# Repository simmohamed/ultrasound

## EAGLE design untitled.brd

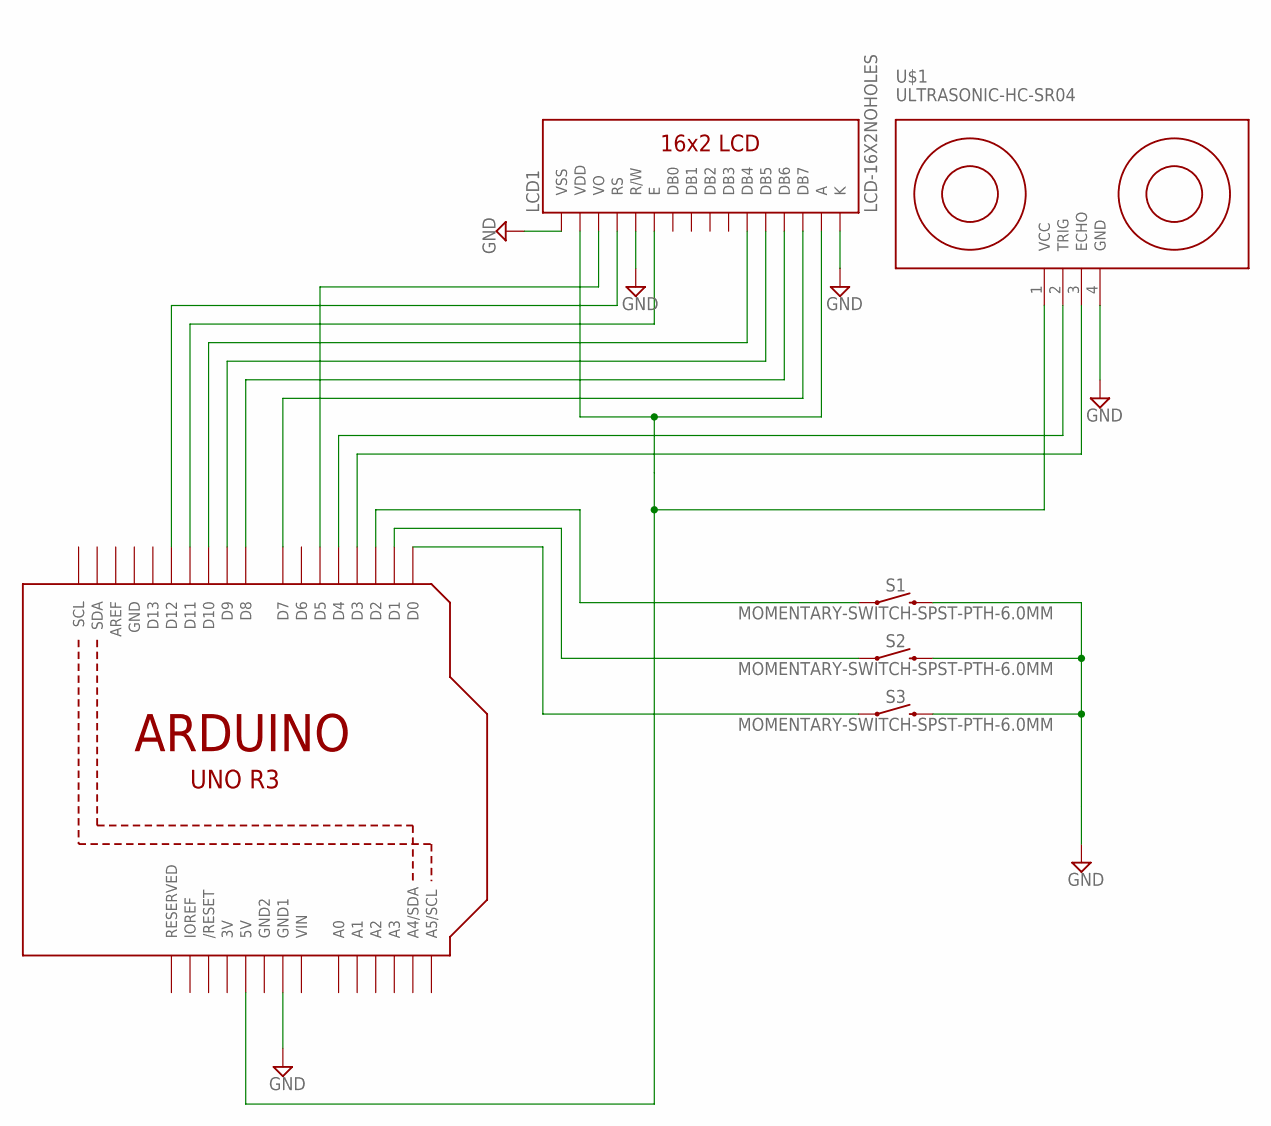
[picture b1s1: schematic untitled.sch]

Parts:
LCD1: LCD-16X2NOHOLES; LCD-16X2_NOHOLESNOSILK
S1, S2, S3: MOMENTARY-SWITCH-SPST-PTH-6.0MM; TACTILE_SWITCH_PTH_6.0MM
U1: ARDUINOR3-BPLACE
U$1: ULTRASONIC-HC-SR04

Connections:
3V: U1.3V
GND: LCD1.1 (VSS), LCD1.5 (R/W), LCD1.16 (K), S1.3 (2), S2.3 (2), S3.3 (2), U1.GND, U1.GND1, U$1.4 (GND)
GND2: U1.GND2
unnamed: LCD1.6 (E), U1.D11
unnamed: LCD1.4 (RS), U1.D12
unnamed: LCD1.11 (DB4), U1.D10
unnamed: LCD1.12 (DB5), U1.D9
unnamed: LCD1.13 (DB6), U1.D8
unnamed: LCD1.14 (DB7), U1.D7
unnamed: LCD1.2 (VDD), LCD1.15 (A), U1.5V, U$1.1 (VCC)
unnamed: LCD1.3 (VO), U1.D5
unnamed: U1.D3, U$1.3 (ECHO)
unnamed: U1.D4, U$1.2 (TRIG)
unnamed: S3.1, U1.D0
unnamed: S2.1, U1.D1
unnamed: S1.1, U1.D2
VIN: U1.VIN

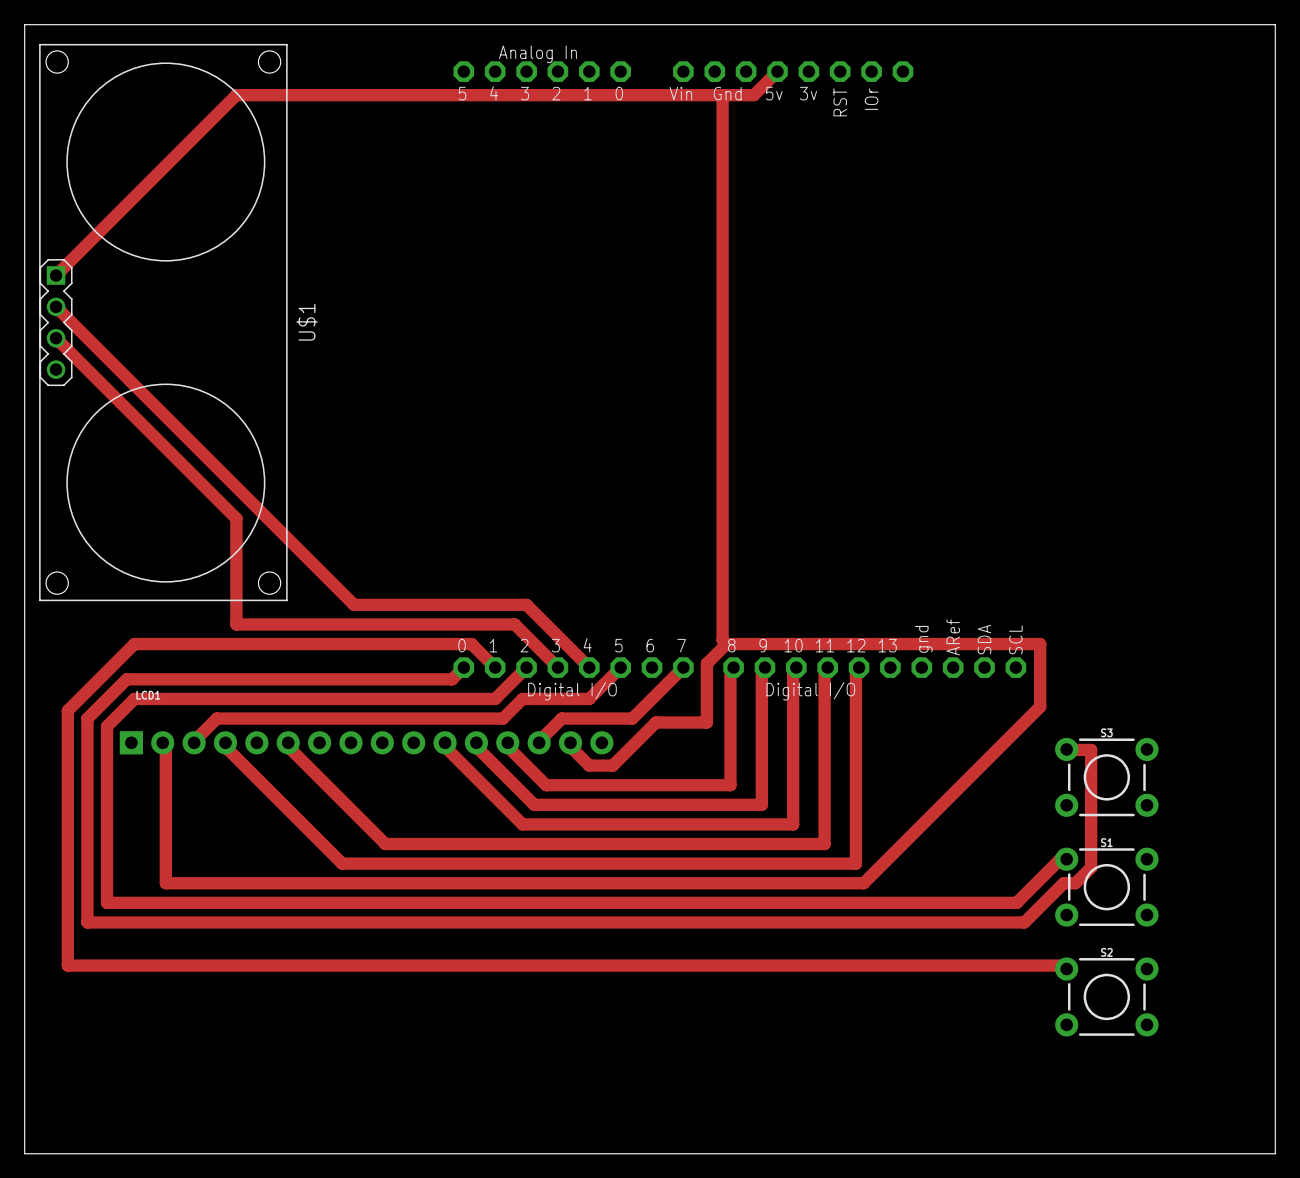
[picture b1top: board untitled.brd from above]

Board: 2 copper layers, 101.3 x 91.4 mm, 6 parts (0 on the bottom side), 14 nets.

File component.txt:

Partlist exported from //fs1/homeFolders$/mohamed.rabbal/Documents/EAGLE/projects/ultra sonic/ultra sonic/untitled.sch at 12/4/2018 10:03 AM

Part Value                           Device                          Package                  Description                                                                                                                 PROD_ID     SF_ID     SF_SKU   
LCD1 LCD-16X2NOHOLES                 LCD-16X2NOHOLES                 LCD-16X2_NOHOLESNOSILK   Standard text-only 16x2 parallel input LCD                                                                                              LCD-00255          
S1   MOMENTARY-SWITCH-SPST-PTH-6.0MM MOMENTARY-SWITCH-SPST-PTH-6.0MM TACTILE_SWITCH_PTH_6.0MM Momentary Switch (Pushbutton) - SPST                                                                                         SWCH-08441           COM-00097
S2   MOMENTARY-SWITCH-SPST-PTH-6.0MM MOMENTARY-SWITCH-SPST-PTH-6.0MM TACTILE_SWITCH_PTH_6.0MM Momentary Switch (Pushbutton) - SPST                                                                                         SWCH-08441           COM-00097
S3   MOMENTARY-SWITCH-SPST-PTH-6.0MM MOMENTARY-SWITCH-SPST-PTH-6.0MM TACTILE_SWITCH_PTH_6.0MM Momentary Switch (Pushbutton) - SPST                                                                                         SWCH-08441           COM-00097
U$1  ULTRASONIC-HC-SR04              ULTRASONIC-HC-SR04              ULTRASONIC-HC-SR04       Ultrasonic Ranging Module HC-SR04                                                                                                                          
U1   ARDUINOR3-BPLACE                ARDUINOR3-BPLACE                ARDUINOR3-BPLACE         This is a new object for the new Arduino R3 - with extra pins that you may want to use (such as IOref, and duplicated A4/A5

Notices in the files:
parts and their libraries:
SparkFun-Displays: Licensing: Creative Commons ShareAlike 4.0 International - https://creativecommons.org/licenses/by-sa/4.0
diy-modules: Released under the Creative Commons Attribution 4.0 International License: http://creativecommons.org/licenses/by/4.0
